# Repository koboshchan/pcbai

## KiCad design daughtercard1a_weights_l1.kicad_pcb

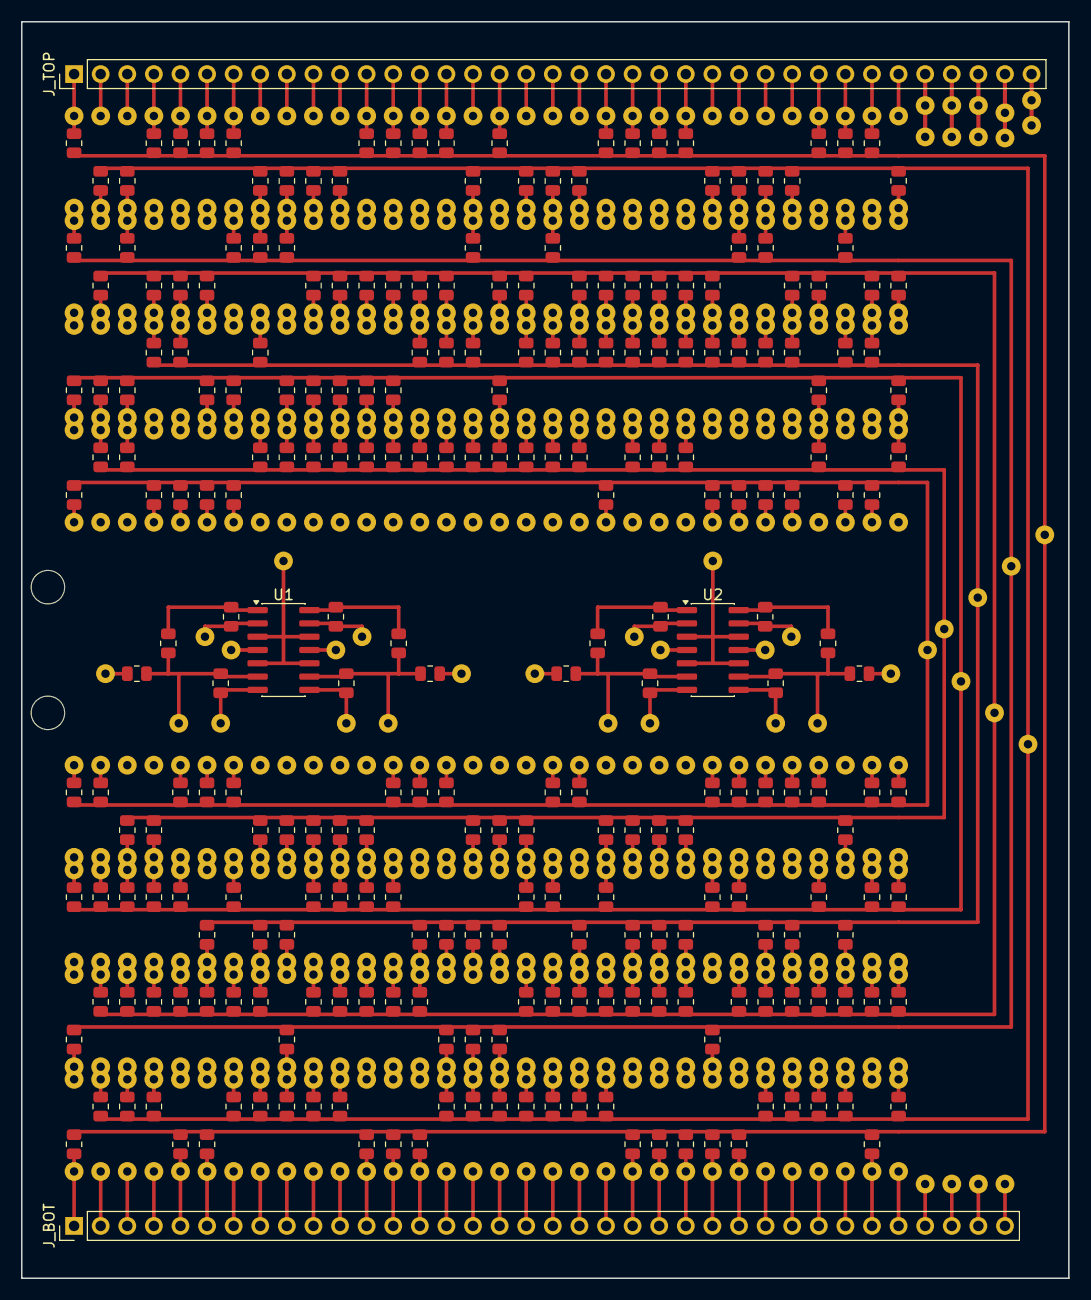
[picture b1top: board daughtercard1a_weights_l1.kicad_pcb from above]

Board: 2 copper layers, 100.0 x 120.0 mm, 556 parts (0 on the bottom side), 85 nets.

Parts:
J_BOT: INPUTS_32_63_SUM; PinHeader_1x36_P2.54mm_Vertical
J_TOP: INPUTS_0_31_PWR; PinHeader_1x37_P2.54mm_Vertical
MH1, MH2: MountingHole_3.2mm_M3
R1_0_0, R1_4_0, R1_7_0, R1_21_0, R1_22_0, R1_26_3, R1_27_0, R1_40_3, R1_55_0, R1_62_0, R1_63_3: 12k; R_0805_2012Metric
R1_0_1, R1_3_3, R1_6_1, R1_13_1, R1_14_1, R1_15_0, R1_25_1, R1_27_1, R1_48_1, R1_50_3: 300k; R_0805_2012Metric
R1_0_2, R1_6_3, R1_11_1, R1_12_1, R1_20_0, R1_30_1, R1_34_2, R1_38_0, R1_38_2, R1_40_0, R1_44_1, R1_45_0, R1_45_1, R1_46_2, R1_49_1, R1_50_1, R1_53_1, R1_53_3, R1_59_1, R1_60_1, R1_62_2: 51k; R_0805_2012Metric
R1_0_3, R1_3_2, R1_11_3, R1_13_2, R1_18_0, R1_27_2, R1_35_2, R1_37_0, R1_48_2, R1_49_0, R1_57_2, R1_60_0: 43k; R_0805_2012Metric
R1_1_0, R1_1_2, R1_7_1, R1_10_0, R1_10_2, R1_16_1, R1_18_1, R1_19_1, R1_20_3, R1_21_3, R1_24_1, R1_28_0, R1_28_3, R1_31_1, R1_33_1, R1_34_1, R1_35_0, R1_36_3, R1_37_1, R1_39_2, R1_39_3, R1_44_2, R1_44_3, R1_46_1, R1_50_0, R1_51_2, R1_52_1, R1_52_3, R1_53_2, R1_54_3, R1_57_0, R1_58_0, R1_58_3, R1_59_0, R1_62_1: 200k; R_0805_2012Metric
R1_1_1, R1_5_3, R1_26_1, R1_31_0, R1_46_3, R1_47_1, R1_48_0: 390k; R_0805_2012Metric
R1_1_3, R1_4_1, R1_5_1, R1_6_0, R1_8_1, R1_10_1, R1_11_0, R1_17_0, R1_22_3, R1_29_3, R1_30_2, R1_32_0, R1_32_1, R1_32_2, R1_35_1, R1_36_2, R1_37_2, R1_42_3, R1_43_0, R1_44_0, R1_46_0, R1_48_3, R1_50_2, R1_51_1, R1_51_3, R1_52_2, R1_53_0, R1_54_1, R1_57_1, R1_59_2, R1_61_2, R1_62_3: 75k; R_0805_2012Metric
R1_2_0, R1_2_2, R1_8_0, R1_8_2, R1_14_2, R1_16_0, R1_18_2, R1_23_3, R1_24_0, R1_26_2, R1_29_0, R1_36_0, R1_38_3, R1_41_3, R1_42_2, R1_43_2, R1_47_3, R1_49_3, R1_54_0, R1_54_2, R1_55_2, R1_55_3, R1_59_3: 22k; R_0805_2012Metric
R1_2_1, R1_2_3, R1_3_0, R1_3_1, R1_9_1, R1_11_2, R1_12_2, R1_12_3, R1_14_3, R1_15_1, R1_17_1, R1_21_1, R1_23_1, R1_28_2, R1_31_3, R1_33_0, R1_33_2, R1_36_1, R1_38_1, R1_39_1, R1_41_1, R1_42_1, R1_43_1, R1_45_3, R1_51_0, R1_52_0, R1_55_1, R1_58_1, R1_58_2, R1_60_2, R1_61_1, R1_63_1: 100k; R_0805_2012Metric
R1_4_2, R1_4_3, R1_5_0, R1_5_2, R1_9_0, R1_9_3, R1_10_3, R1_13_0, R1_14_0, R1_16_2, R1_17_2, R1_19_2, R1_24_2, R1_25_0, R1_26_0, R1_27_3, R1_30_3, R1_33_3, R1_34_0, R1_37_3, R1_40_2, R1_41_2, R1_42_0, R1_43_3, R1_47_0, R1_49_2, R1_56_3, R1_57_3, R1_63_2: 33k; R_0805_2012Metric
R1_6_2, R1_61_0, R1_63_0: 680k; R_0805_2012Metric
R1_7_2, R1_15_2, R1_17_3, R1_19_0, R1_21_2, R1_25_3, R1_56_0: 10k; R_0805_2012Metric
R1_7_3, R1_9_2, R1_19_3, R1_20_2, R1_30_0, R1_41_0: 20k; R_0805_2012Metric
R1_8_3, R1_12_0, R1_35_3: 18k; R_0805_2012Metric
R1_13_3, R1_20_1, R1_22_1, R1_28_1, R1_29_1, R1_40_1, R1_61_3: 1M; R_0805_2012Metric
R1_15_3, R1_18_3, R1_23_0, R1_29_2: 15k; R_0805_2012Metric
R1_16_3, R1_22_2, R1_23_2, R1_24_3, R1_31_2, R1_39_0: 7.5k; R_0805_2012Metric
R1_25_2, R1_45_2, R1_47_2, R1_60_3: 47k; R_0805_2012Metric
R1_32_3: 5.6k; R_0805_2012Metric
R1_34_3, R1_56_2: 470k; R_0805_2012Metric
R1_56_1: DNP; R_0805_2012Metric
Rb_N0: 390k; R_0805_2012Metric
Rb_N1: 470k; R_0805_2012Metric
Rb_N2, Rb_N3: 200k; R_0805_2012Metric
Rc_N0, Rc_N1, Rc_N2, Rc_N3: 10k; R_0805_2012Metric
Rf1_N0, Rf1_N1, Rf1_N2, Rf1_N3: 10k; R_0805_2012Metric
Rf_N0, Rf_N1, Rf_N2, Rf_N3: 10k; R_0805_2012Metric
U1, U2: TL074; SOIC-14_3.9x8.7mm_P1.27mm
W1, W2, W3, W4, W5, W6, W7, W8, W9, W10, W11, W12, W13, W14, W15, W16, W17, W18, W19, W20, W21, W22, W23, W24, W25, W26, W27, W28, W29, W30, W31, W32, W33, W34, W35, W36, W37, W38, W39, W40, W41, W42, W43, W44, W45, W46, W47, W48, W49, W50, W51, W52, W53, W54, W55, W56, W57, W58, W59, W60, W61, W62, W63, W64, W65, W66, W67, W68, W69, W70, W71, W72, W73, W74, W75, W76, W77, W78, W79, W80, W81, W82, W83, W84, W85, W86, W87, W88, W89, W90, W91, W92, W93, W94, W95, W96, W97, W98, W99, W100, W101, W102, W103, W104, W105, W106, W107, W108, W109, W110, W111, W112, W113, W114, W115, W116, W117, W118, W119, W120, W121, W122, W123, W124, W125, W126, W127, W128, W129, W130, W131, W132, W133, W134, W135, W136, W137, W138, W139, W140, W141, W142, W143, W144, W145, W146, W147, W148, W149, W150, W151, W152, W153, W154, W155, W156, W157, W158, W159, W160, W161, W162, W163, W164, W165, W166, W167, W168, W169, W170, W171, W172, W173, W174, W175, W176, W177, W178, W179, W180, W181, W182, W183, W184, W185, W186, W187, W188, W189, W190, W191, W192, W193, W194, W195, W196, W197, W198, W199, W200, W201, W202, W203, W204, W205, W206, W207, W208, W209, W210, W211, W212, W213, W214, W215, W216, W217, W218, W219, W220, W221, W222, W223, W224, W225, W226, W227, W228, W229, W230, W231, W232, W233, W234, W235, W236, W237, W238, W239, W240, W241, W242, W243, W244, W245, W246, W247, W248, W249, W250, W251, W252, W253, W254, W255, W256, W257, W258, W259, W260, W261, W262, W263, W264, W265, W266, W267, W268, W269, W270, W271, W272, W273, W274, W275, W276, W277, W278: JUMPER; Jumper_Wire

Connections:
+5V_REF: J_TOP.36, Rb_N1.2, Rb_N3.2, W270.1, W278.1
+12V: J_TOP.33, U1.4, U2.4, W259.1, W261.1
-5V_REF: J_TOP.37, Rb_N0.1, Rb_N2.1, W266.1, W274.1
-12V: J_TOP.34, U1.11, U2.11, W260.1, W262.1
GND: J_TOP.35, U1.3, U1.5, U1.10, U1.12, U2.3, U2.5, U2.10, U2.12, W257.1, W258.1
IN_0: J_TOP.1, R1_0_0.1, R1_0_1.1, R1_0_2.1, R1_0_3.1, W1.1, W2.1, W3.1, W4.1
IN_1: J_TOP.2, R1_1_0.1, R1_1_1.1, R1_1_2.1, R1_1_3.1, W5.1, W6.1, W7.1, W8.1
IN_2: J_TOP.3, R1_2_0.1, R1_2_1.1, R1_2_2.1, R1_2_3.1, W9.1, W10.1, W11.1, W12.1
IN_3: J_TOP.4, R1_3_0.1, R1_3_1.1, R1_3_2.1, R1_3_3.1, W13.1, W14.1, W15.1, W16.1
IN_4: J_TOP.5, R1_4_0.1, R1_4_1.1, R1_4_2.1, R1_4_3.1, W17.1, W18.1, W19.1, W20.1
IN_5: J_TOP.6, R1_5_0.1, R1_5_1.1, R1_5_2.1, R1_5_3.1, W21.1, W22.1, W23.1, W24.1
IN_6: J_TOP.7, R1_6_0.1, R1_6_1.1, R1_6_2.1, R1_6_3.1, W25.1, W26.1, W27.1, W28.1
IN_7: J_TOP.8, R1_7_0.1, R1_7_1.1, R1_7_2.1, R1_7_3.1, W29.1, W30.1, W31.1, W32.1
IN_8: J_TOP.9, R1_8_0.1, R1_8_1.1, R1_8_2.1, R1_8_3.1, W33.1, W34.1, W35.1, W36.1
IN_9: J_TOP.10, R1_9_0.1, R1_9_1.1, R1_9_2.1, R1_9_3.1, W37.1, W38.1, W39.1, W40.1
IN_10: J_TOP.11, R1_10_0.1, R1_10_1.1, R1_10_2.1, R1_10_3.1, W41.1, W42.1, W43.1, W44.1
IN_11: J_TOP.12, R1_11_0.1, R1_11_1.1, R1_11_2.1, R1_11_3.1, W45.1, W46.1, W47.1, W48.1
IN_12: J_TOP.13, R1_12_0.1, R1_12_1.1, R1_12_2.1, R1_12_3.1, W49.1, W50.1, W51.1, W52.1
IN_13: J_TOP.14, R1_13_0.1, R1_13_1.1, R1_13_2.1, R1_13_3.1, W53.1, W54.1, W55.1, W56.1
IN_14: J_TOP.15, R1_14_0.1, R1_14_1.1, R1_14_2.1, R1_14_3.1, W57.1, W58.1, W59.1, W60.1
IN_15: J_TOP.16, R1_15_0.1, R1_15_1.1, R1_15_2.1, R1_15_3.1, W61.1, W62.1, W63.1, W64.1
IN_16: J_TOP.17, R1_16_0.1, R1_16_1.1, R1_16_2.1, R1_16_3.1, W65.1, W66.1, W67.1, W68.1
IN_17: J_TOP.18, R1_17_0.1, R1_17_1.1, R1_17_2.1, R1_17_3.1, W69.1, W70.1, W71.1, W72.1
IN_18: J_TOP.19, R1_18_0.1, R1_18_1.1, R1_18_2.1, R1_18_3.1, W73.1, W74.1, W75.1, W76.1
IN_19: J_TOP.20, R1_19_0.1, R1_19_1.1, R1_19_2.1, R1_19_3.1, W77.1, W78.1, W79.1, W80.1
IN_20: J_TOP.21, R1_20_0.1, R1_20_1.1, R1_20_2.1, R1_20_3.1, W81.1, W82.1, W83.1, W84.1
IN_21: J_TOP.22, R1_21_0.1, R1_21_1.1, R1_21_2.1, R1_21_3.1, W85.1, W86.1, W87.1, W88.1
IN_22: J_TOP.23, R1_22_0.1, R1_22_1.1, R1_22_2.1, R1_22_3.1, W89.1, W90.1, W91.1, W92.1
IN_23: J_TOP.24, R1_23_0.1, R1_23_1.1, R1_23_2.1, R1_23_3.1, W93.1, W94.1, W95.1, W96.1
IN_24: J_TOP.25, R1_24_0.1, R1_24_1.1, R1_24_2.1, R1_24_3.1, W97.1, W98.1, W99.1, W100.1
IN_25: J_TOP.26, R1_25_0.1, R1_25_1.1, R1_25_2.1, R1_25_3.1, W101.1, W102.1, W103.1, W104.1
IN_26: J_TOP.27, R1_26_0.1, R1_26_1.1, R1_26_2.1, R1_26_3.1, W105.1, W106.1, W107.1, W108.1
IN_27: J_TOP.28, R1_27_0.1, R1_27_1.1, R1_27_2.1, R1_27_3.1, W109.1, W110.1, W111.1, W112.1
IN_28: J_TOP.29, R1_28_0.1, R1_28_1.1, R1_28_2.1, R1_28_3.1, W113.1, W114.1, W115.1, W116.1
IN_29: J_TOP.30, R1_29_0.1, R1_29_1.1, R1_29_2.1, R1_29_3.1, W117.1, W118.1, W119.1, W120.1
IN_30: J_TOP.31, R1_30_0.1, R1_30_1.1, R1_30_2.1, R1_30_3.1, W121.1, W122.1, W123.1, W124.1
IN_31: J_TOP.32, R1_31_0.1, R1_31_1.1, R1_31_2.1, R1_31_3.1, W125.1, W126.1, W127.1, W128.1
IN_32: J_BOT.1, R1_32_0.1, R1_32_1.1, R1_32_2.1, R1_32_3.1, W129.1, W130.1, W131.1, W132.1
IN_33: J_BOT.2, R1_33_0.1, R1_33_1.1, R1_33_2.1, R1_33_3.1, W133.1, W134.1, W135.1, W136.1
IN_34: J_BOT.3, R1_34_0.1, R1_34_1.1, R1_34_2.1, R1_34_3.1, W137.1, W138.1, W139.1, W140.1
IN_35: J_BOT.4, R1_35_0.1, R1_35_1.1, R1_35_2.1, R1_35_3.1, W141.1, W142.1, W143.1, W144.1
IN_36: J_BOT.5, R1_36_0.1, R1_36_1.1, R1_36_2.1, R1_36_3.1, W145.1, W146.1, W147.1, W148.1
IN_37: J_BOT.6, R1_37_0.1, R1_37_1.1, R1_37_2.1, R1_37_3.1, W149.1, W150.1, W151.1, W152.1
IN_38: J_BOT.7, R1_38_0.1, R1_38_1.1, R1_38_2.1, R1_38_3.1, W153.1, W154.1, W155.1, W156.1
IN_39: J_BOT.8, R1_39_0.1, R1_39_1.1, R1_39_2.1, R1_39_3.1, W157.1, W158.1, W159.1, W160.1
IN_40: J_BOT.9, R1_40_0.1, R1_40_1.1, R1_40_2.1, R1_40_3.1, W161.1, W162.1, W163.1, W164.1
IN_41: J_BOT.10, R1_41_0.1, R1_41_1.1, R1_41_2.1, R1_41_3.1, W165.1, W166.1, W167.1, W168.1
IN_42: J_BOT.11, R1_42_0.1, R1_42_1.1, R1_42_2.1, R1_42_3.1, W169.1, W170.1, W171.1, W172.1
IN_43: J_BOT.12, R1_43_0.1, R1_43_1.1, R1_43_2.1, R1_43_3.1, W173.1, W174.1, W175.1, W176.1
IN_44: J_BOT.13, R1_44_0.1, R1_44_1.1, R1_44_2.1, R1_44_3.1, W177.1, W178.1, W179.1, W180.1
IN_45: J_BOT.14, R1_45_0.1, R1_45_1.1, R1_45_2.1, R1_45_3.1, W181.1, W182.1, W183.1, W184.1
IN_46: J_BOT.15, R1_46_0.1, R1_46_1.1, R1_46_2.1, R1_46_3.1, W185.1, W186.1, W187.1, W188.1
IN_47: J_BOT.16, R1_47_0.1, R1_47_1.1, R1_47_2.1, R1_47_3.1, W189.1, W190.1, W191.1, W192.1
IN_48: J_BOT.17, R1_48_0.1, R1_48_1.1, R1_48_2.1, R1_48_3.1, W193.1, W194.1, W195.1, W196.1
IN_49: J_BOT.18, R1_49_0.1, R1_49_1.1, R1_49_2.1, R1_49_3.1, W197.1, W198.1, W199.1, W200.1
IN_50: J_BOT.19, R1_50_0.1, R1_50_1.1, R1_50_2.1, R1_50_3.1, W201.1, W202.1, W203.1, W204.1
IN_51: J_BOT.20, R1_51_0.1, R1_51_1.1, R1_51_2.1, R1_51_3.1, W205.1, W206.1, W207.1, W208.1
IN_52: J_BOT.21, R1_52_0.1, R1_52_1.1, R1_52_2.1, R1_52_3.1, W209.1, W210.1, W211.1, W212.1
IN_53: J_BOT.22, R1_53_0.1, R1_53_1.1, R1_53_2.1, R1_53_3.1, W213.1, W214.1, W215.1, W216.1
IN_54: J_BOT.23, R1_54_0.1, R1_54_1.1, R1_54_2.1, R1_54_3.1, W217.1, W218.1, W219.1, W220.1
IN_55: J_BOT.24, R1_55_0.1, R1_55_1.1, R1_55_2.1, R1_55_3.1, W221.1, W222.1, W223.1, W224.1
IN_56: J_BOT.25, R1_56_0.1, R1_56_1.1, R1_56_2.1, R1_56_3.1, W225.1, W226.1, W227.1, W228.1
IN_57: J_BOT.26, R1_57_0.1, R1_57_1.1, R1_57_2.1, R1_57_3.1, W229.1, W230.1, W231.1, W232.1
IN_58: J_BOT.27, R1_58_0.1, R1_58_1.1, R1_58_2.1, R1_58_3.1, W233.1, W234.1, W235.1, W236.1
IN_59: J_BOT.28, R1_59_0.1, R1_59_1.1, R1_59_2.1, R1_59_3.1, W237.1, W238.1, W239.1, W240.1
IN_60: J_BOT.29, R1_60_0.1, R1_60_1.1, R1_60_2.1, R1_60_3.1, W241.1, W242.1, W243.1, W244.1
IN_61: J_BOT.30, R1_61_0.1, R1_61_1.1, R1_61_2.1, R1_61_3.1, W245.1, W246.1, W247.1, W248.1
IN_62: J_BOT.31, R1_62_0.1, R1_62_1.1, R1_62_2.1, R1_62_3.1, W249.1, W250.1, W251.1, W252.1
IN_63: J_BOT.32, R1_63_0.1, R1_63_1.1, R1_63_2.1, R1_63_3.1, W253.1, W254.1, W255.1, W256.1
SUM_NEG_0: R1_1_0.2, R1_2_0.2, R1_7_0.2, R1_8_0.2, R1_9_0.2, R1_10_0.2, R1_15_0.2, R1_17_0.2, R1_18_0.2, R1_19_0.2, R1_24_0.2, R1_25_0.2, R1_26_0.2, R1_27_0.2, R1_31_0.2, R1_33_0.2, R1_34_0.2, R1_35_0.2, R1_38_0.2, R1_39_0.2, R1_40_0.2, R1_41_0.2, R1_42_0.2, R1_46_0.2, R1_47_0.2, R1_48_0.2, R1_49_0.2, R1_50_0.2, R1_51_0.2, R1_52_0.2, R1_58_0.2, R1_59_0.2, R1_60_0.2, R1_61_0.2, R1_63_0.2, Rb_N0.2, Rc_N0.2, Rf_N0.1, U1.6, W265.1
SUM_NEG_1: R1_1_1.2, R1_3_1.2, R1_4_1.2, R1_5_1.2, R1_9_1.2, R1_10_1.2, R1_11_1.2, R1_12_1.2, R1_13_1.2, R1_14_1.2, R1_16_1.2, R1_17_1.2, R1_19_1.2, R1_20_1.2, R1_21_1.2, R1_22_1.2, R1_23_1.2, R1_24_1.2, R1_27_1.2, R1_28_1.2, R1_30_1.2, R1_31_1.2, R1_33_1.2, R1_34_1.2, R1_35_1.2, R1_36_1.2, R1_37_1.2, R1_38_1.2, R1_39_1.2, R1_41_1.2, R1_42_1.2, R1_43_1.2, R1_44_1.2, R1_45_1.2, R1_49_1.2, R1_50_1.2, R1_51_1.2, R1_52_1.2, R1_53_1.2, R1_54_1.2, R1_55_1.2, R1_57_1.2, R1_58_1.2, R1_59_1.2, R1_60_1.2, R1_61_1.2, R1_62_1.2, R1_63_1.2, Rb_N1.1, Rc_N1.2, Rf_N1.1, U1.9, W269.1
SUM_NEG_2: R1_0_2.2, R1_1_2.2, R1_2_2.2, R1_5_2.2, R1_6_2.2, R1_8_2.2, R1_9_2.2, R1_10_2.2, R1_11_2.2, R1_12_2.2, R1_16_2.2, R1_28_2.2, R1_31_2.2, R1_32_2.2, R1_33_2.2, R1_34_2.2, R1_35_2.2, R1_36_2.2, R1_38_2.2, R1_41_2.2, R1_42_2.2, R1_43_2.2, R1_44_2.2, R1_49_2.2, R1_50_2.2, R1_52_2.2, R1_56_2.2, R1_57_2.2, R1_60_2.2, R1_62_2.2, R1_63_2.2, Rb_N2.2, Rc_N2.2, Rf_N2.1, U2.6, W273.1
SUM_NEG_3: R1_0_3.2, R1_3_3.2, R1_4_3.2, R1_5_3.2, R1_6_3.2, R1_20_3.2, R1_24_3.2, R1_25_3.2, R1_26_3.2, R1_27_3.2, R1_29_3.2, R1_30_3.2, R1_32_3.2, R1_33_3.2, R1_36_3.2, R1_37_3.2, R1_38_3.2, R1_44_3.2, R1_45_3.2, R1_46_3.2, R1_50_3.2, R1_51_3.2, R1_56_3.2, R1_57_3.2, R1_58_3.2, R1_59_3.2, R1_60_3.2, R1_62_3.2, R1_63_3.2, Rb_N3.1, Rc_N3.2, Rf_N3.1, U2.9, W277.1
SUM_POS_0: R1_0_0.2, R1_3_0.2, R1_4_0.2, R1_5_0.2, R1_6_0.2, R1_11_0.2, R1_12_0.2, R1_13_0.2, R1_14_0.2, R1_16_0.2, R1_20_0.2, R1_21_0.2, R1_22_0.2, R1_23_0.2, R1_28_0.2, R1_29_0.2, R1_30_0.2, R1_32_0.2, R1_36_0.2, R1_37_0.2, R1_43_0.2, R1_44_0.2, R1_45_0.2, R1_53_0.2, R1_54_0.2, R1_55_0.2, R1_56_0.2, R1_57_0.2, R1_62_0.2, Rf1_N0.2, U1.2, W263.1
SUM_POS_1: R1_0_1.2, R1_2_1.2, R1_6_1.2, R1_7_1.2, R1_8_1.2, R1_15_1.2, R1_18_1.2, R1_25_1.2, R1_26_1.2, R1_29_1.2, R1_32_1.2, R1_40_1.2, R1_46_1.2, R1_47_1.2, R1_48_1.2, R1_56_1.2, Rf1_N1.2, U1.13, W267.1
SUM_POS_2: R1_3_2.2, R1_4_2.2, R1_7_2.2, R1_13_2.2, R1_14_2.2, R1_15_2.2, R1_17_2.2, R1_18_2.2, R1_19_2.2, R1_20_2.2, R1_21_2.2, R1_22_2.2, R1_23_2.2, R1_24_2.2, R1_25_2.2, R1_26_2.2, R1_27_2.2, R1_29_2.2, R1_30_2.2, R1_37_2.2, R1_39_2.2, R1_40_2.2, R1_45_2.2, R1_46_2.2, R1_47_2.2, R1_48_2.2, R1_51_2.2, R1_53_2.2, R1_54_2.2, R1_55_2.2, R1_58_2.2, R1_59_2.2, R1_61_2.2, Rf1_N2.2, U2.2, W271.1
SUM_POS_3: R1_1_3.2, R1_2_3.2, R1_7_3.2, R1_8_3.2, R1_9_3.2, R1_10_3.2, R1_11_3.2, R1_12_3.2, R1_13_3.2, R1_14_3.2, R1_15_3.2, R1_16_3.2, R1_17_3.2, R1_18_3.2, R1_19_3.2, R1_21_3.2, R1_22_3.2, R1_23_3.2, R1_28_3.2, R1_31_3.2, R1_34_3.2, R1_35_3.2, R1_39_3.2, R1_40_3.2, R1_41_3.2, R1_42_3.2, R1_43_3.2, R1_47_3.2, R1_48_3.2, R1_49_3.2, R1_52_3.2, R1_53_3.2, R1_54_3.2, R1_55_3.2, R1_61_3.2, Rf1_N3.2, U2.13, W275.1
V_INV_0: Rc_N0.1, Rf1_N0.1, U1.1
V_INV_1: Rc_N1.1, Rf1_N1.1, U1.14
V_INV_2: Rc_N2.1, Rf1_N2.1, U2.1
V_INV_3: Rc_N3.1, Rf1_N3.1, U2.14
V_SUM_0: J_BOT.33, Rf_N0.2, U1.7, W264.1
V_SUM_1: J_BOT.34, Rf_N1.2, U1.8, W268.1
V_SUM_2: J_BOT.35, Rf_N2.2, U2.7, W272.1
V_SUM_3: J_BOT.36, Rf_N3.2, U2.8, W276.1

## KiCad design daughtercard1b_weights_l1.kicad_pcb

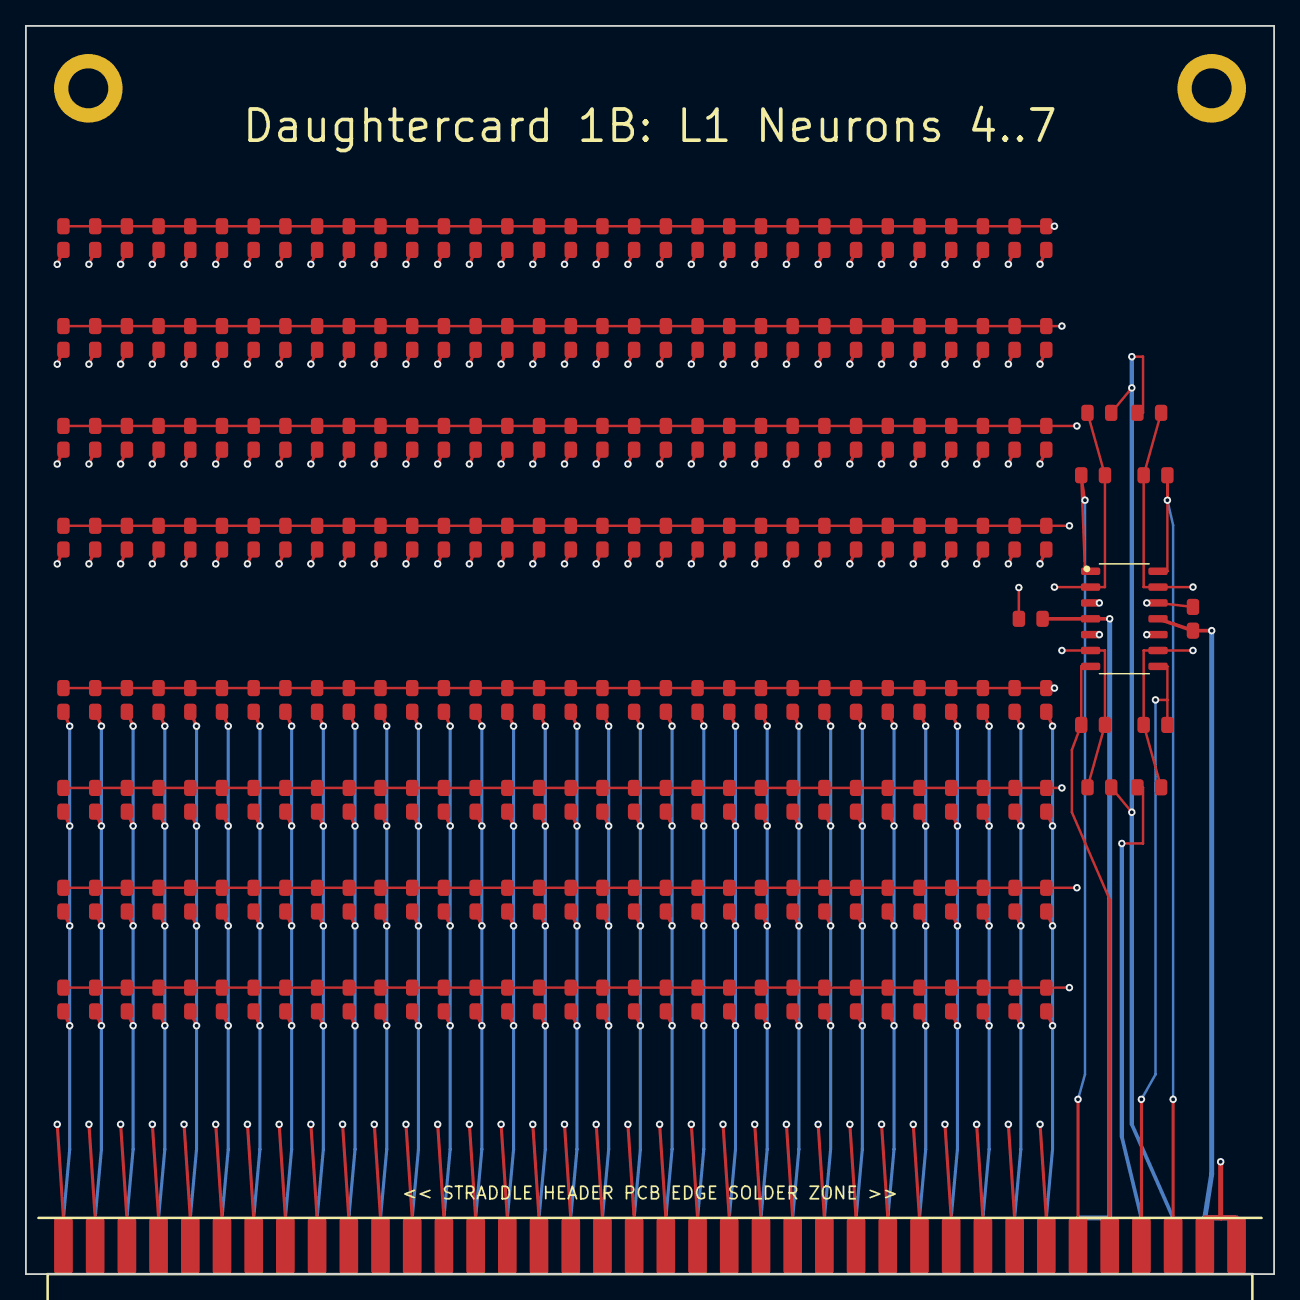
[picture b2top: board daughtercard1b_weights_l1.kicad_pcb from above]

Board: 4 copper layers, 100.0 x 100.0 mm, 270 parts (0 on the bottom side), 77 nets.

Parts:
C_U1N, C_U1P: 0.1uF; C_0805_2012Metric
H1, H2: MountingHole; MountingHole_3.2mm_M3_Pad
J_STRADDLE_EDGE: PinHeader_2x38_Straddle; PinHeader_2x38_Straddle_P2.54mm
R1_0_0, R1_1_3, R1_5_3, R1_6_3, R1_7_2, R1_21_2, R1_22_2, R1_32_0, R1_39_2, R1_42_0, R1_47_3, R1_56_2, R1_62_2: 7.5k; R_0805_2012Metric
R1_0_1, R1_6_2, R1_29_3, R1_41_0: 5.6k; R_0805_2012Metric
R1_0_2, R1_1_0, R1_3_1, R1_3_3, R1_8_0, R1_8_1, R1_10_1, R1_27_0, R1_28_2, R1_28_3, R1_33_2, R1_36_0, R1_40_2, R1_41_1, R1_45_2, R1_46_2, R1_48_2, R1_54_0, R1_57_3, R1_62_1: 18k; R_0805_2012Metric
R1_0_3, R1_40_0, R1_56_1: 5.1k; R_0805_2012Metric
R1_1_1, R1_1_2, R1_6_1, R1_7_0, R1_9_0, R1_10_0, R1_10_2, R1_11_2, R1_21_3, R1_25_3, R1_29_0, R1_35_2, R1_42_2, R1_42_3, R1_44_2, R1_47_2, R1_48_1, R1_53_2, R1_55_0, R1_56_0, R1_56_3, R1_58_1, R1_60_0, R1_60_1: 43k; R_0805_2012Metric
R1_2_0, R1_3_2, R1_15_1, R1_17_1, R1_17_3, R1_22_1, R1_26_0, R1_26_1, R1_33_0, R1_34_0, R1_37_0, R1_37_1, R1_49_3, R1_55_2, R1_58_3, R1_59_0, R1_60_3, R1_61_3: 51k; R_0805_2012Metric
R1_2_1, R1_3_0, R1_4_0, R1_5_1, R1_8_2, R1_11_1, R1_12_2, R1_13_3, R1_14_3, R1_16_0, R1_18_0, R1_23_0, R1_29_2, R1_33_3, R1_35_1, R1_36_2, R1_37_3, R1_44_0, R1_44_3, R1_45_0, R1_45_1, R1_53_0, R1_54_3, R1_57_2, R1_58_0, R1_59_1, R1_60_2, R1_61_0, R1_62_0: 33k; R_0805_2012Metric
R1_2_2, R1_21_1, R1_24_2, R1_41_3: 300k; R_0805_2012Metric
R1_2_3, R1_4_1, R1_11_0, R1_15_0, R1_19_1, R1_19_2, R1_20_0, R1_20_1, R1_24_3, R1_28_0, R1_32_2, R1_32_3, R1_33_1, R1_34_1, R1_38_2, R1_43_2, R1_46_0, R1_46_3, R1_51_1, R1_54_2, R1_59_3, R1_62_3, R1_63_1, R1_63_2: 22k; R_0805_2012Metric
R1_4_2, R1_24_1, R1_30_0, R1_30_2, R1_31_1, R1_38_0, R1_38_3, R1_39_0, R1_43_1, R1_48_0, R1_50_0, R1_51_0: 15k; R_0805_2012Metric
R1_4_3, R1_5_2, R1_8_3, R1_20_2, R1_22_3, R1_31_0, R1_32_1, R1_42_1, R1_43_0, R1_55_3, R1_63_0: 10k; R_0805_2012Metric
R1_5_0, R1_12_0, R1_57_0: 47k; R_0805_2012Metric
R1_6_0, R1_7_3, R1_14_2, R1_15_3, R1_16_2, R1_16_3, R1_23_1, R1_24_0, R1_27_1, R1_40_1, R1_47_1, R1_49_0: 12k; R_0805_2012Metric
R1_7_1, R1_23_2, R1_31_2, R1_63_3: 4.7k; R_0805_2012Metric
R1_9_1, R1_9_3, R1_10_3, R1_12_3, R1_19_0, R1_21_0, R1_29_1, R1_34_2, R1_36_3, R1_37_2, R1_38_1, R1_43_3, R1_46_1, R1_51_2, R1_52_3, R1_53_3, R1_58_2: 100k; R_0805_2012Metric
R1_9_2, R1_14_0, R1_18_3, R1_25_1, R1_27_2, R1_30_1, R1_35_3, R1_36_1, R1_45_3, R1_47_0, R1_48_3, R1_49_2, R1_50_2, R1_52_1, R1_54_1, R1_57_1, R1_59_2, R1_61_1, R1_61_2: 75k; R_0805_2012Metric
R1_11_3, R1_12_1, R1_17_2, R1_26_2, R1_27_3, R1_34_3, R1_50_3, R1_52_2, R1_53_1: 1M; R_0805_2012Metric
R1_13_0, R1_13_1, R1_14_1, R1_16_1, R1_18_1, R1_41_2, R1_49_1, R1_55_1: 200k; R_0805_2012Metric
R1_13_2, R1_25_0, R1_28_1, R1_35_0, R1_39_1, R1_40_3, R1_44_1, R1_52_0: 20k; R_0805_2012Metric
R1_15_2, R1_31_3: 3.3k; R_0805_2012Metric
R1_17_0, R1_20_3, R1_51_3: 390k; R_0805_2012Metric
R1_18_2, R1_19_3, R1_22_0, R1_25_2, R1_26_3, R1_50_1: 470k; R_0805_2012Metric
R1_23_3, R1_39_3: 3k; R_0805_2012Metric
R1_30_3: 2.2k; R_0805_2012Metric
Rb_N4: 22k; R_0805_2012Metric
Rb_N5, Rb_N7: 33k; R_0805_2012Metric
Rb_N6: 100k; R_0805_2012Metric
Rf_N4, Rf_N5, Rf_N6, Rf_N7: 10k; R_0805_2012Metric
U1: TL074; SOIC-14_3.9x8.7mm_P1.27mm

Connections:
+5V_REF: J_STRADDLE_EDGE.B35, Rb_N6.1
+12V: C_U1P.2, J_STRADDLE_EDGE.B33, J_STRADDLE_EDGE.B34, U1.4
-5V_REF: J_STRADDLE_EDGE.B36, Rb_N4.2, Rb_N5.2, Rb_N7.1
-12V: C_U1N.1, J_STRADDLE_EDGE.B37, J_STRADDLE_EDGE.B38, U1.11
GND: C_U1N.2, C_U1P.1, H1.1, H2.1, J_STRADDLE_EDGE.A37, J_STRADDLE_EDGE.A38, U1.3, U1.5, U1.10, U1.12
INV_N4: R1_0_0.2, R1_1_0.2, R1_2_0.2, R1_3_0.2, R1_4_0.2, R1_5_0.2, R1_6_0.2, R1_7_0.2, R1_8_0.2, R1_9_0.2, R1_10_0.2, R1_11_0.2, R1_12_0.2, R1_13_0.2, R1_14_0.2, R1_15_0.2, R1_16_0.2, R1_17_0.2, R1_18_0.2, R1_19_0.2, R1_20_0.2, R1_21_0.2, R1_22_0.2, R1_23_0.2, R1_24_0.2, R1_25_0.2, R1_26_0.2, R1_27_0.2, R1_28_0.2, R1_29_0.2, R1_30_0.2, R1_31_0.2, R1_32_0.2, R1_33_0.2, R1_34_0.2, R1_35_0.2, R1_36_0.2, R1_37_0.2, R1_38_0.2, R1_39_0.2, R1_40_0.2, R1_41_0.2, R1_42_0.2, R1_43_0.2, R1_44_0.2, R1_45_0.2, R1_46_0.2, R1_47_0.2, R1_48_0.2, R1_49_0.2, R1_50_0.2, R1_51_0.2, R1_52_0.2, R1_53_0.2, R1_54_0.2, R1_55_0.2, R1_56_0.2, R1_57_0.2, R1_58_0.2, R1_59_0.2, R1_60_0.2, R1_61_0.2, R1_62_0.2, R1_63_0.2, Rb_N4.1, Rf_N4.2, U1.2
INV_N5: R1_0_1.2, R1_1_1.2, R1_2_1.2, R1_3_1.2, R1_4_1.2, R1_5_1.2, R1_6_1.2, R1_7_1.2, R1_8_1.2, R1_9_1.2, R1_10_1.2, R1_11_1.2, R1_12_1.2, R1_13_1.2, R1_14_1.2, R1_15_1.2, R1_16_1.2, R1_17_1.2, R1_18_1.2, R1_19_1.2, R1_20_1.2, R1_21_1.2, R1_22_1.2, R1_23_1.2, R1_24_1.2, R1_25_1.2, R1_26_1.2, R1_27_1.2, R1_28_1.2, R1_29_1.2, R1_30_1.2, R1_31_1.2, R1_32_1.2, R1_33_1.2, R1_34_1.2, R1_35_1.2, R1_36_1.2, R1_37_1.2, R1_38_1.2, R1_39_1.2, R1_40_1.2, R1_41_1.2, R1_42_1.2, R1_43_1.2, R1_44_1.2, R1_45_1.2, R1_46_1.2, R1_47_1.2, R1_48_1.2, R1_49_1.2, R1_50_1.2, R1_51_1.2, R1_52_1.2, R1_53_1.2, R1_54_1.2, R1_55_1.2, R1_56_1.2, R1_57_1.2, R1_58_1.2, R1_59_1.2, R1_60_1.2, R1_61_1.2, R1_62_1.2, R1_63_1.2, Rb_N5.1, Rf_N5.2, U1.6
INV_N6: R1_0_2.2, R1_1_2.2, R1_2_2.2, R1_3_2.2, R1_4_2.2, R1_5_2.2, R1_6_2.2, R1_7_2.2, R1_8_2.2, R1_9_2.2, R1_10_2.2, R1_11_2.2, R1_12_2.2, R1_13_2.2, R1_14_2.2, R1_15_2.2, R1_16_2.2, R1_17_2.2, R1_18_2.2, R1_19_2.2, R1_20_2.2, R1_21_2.2, R1_22_2.2, R1_23_2.2, R1_24_2.2, R1_25_2.2, R1_26_2.2, R1_27_2.2, R1_28_2.2, R1_29_2.2, R1_30_2.2, R1_31_2.2, R1_32_2.2, R1_33_2.2, R1_34_2.2, R1_35_2.2, R1_36_2.2, R1_37_2.2, R1_38_2.2, R1_39_2.2, R1_40_2.2, R1_41_2.2, R1_42_2.2, R1_43_2.2, R1_44_2.2, R1_45_2.2, R1_46_2.2, R1_47_2.2, R1_48_2.2, R1_49_2.2, R1_50_2.2, R1_51_2.2, R1_52_2.2, R1_53_2.2, R1_54_2.2, R1_55_2.2, R1_56_2.2, R1_57_2.2, R1_58_2.2, R1_59_2.2, R1_60_2.2, R1_61_2.2, R1_62_2.2, R1_63_2.2, Rb_N6.2, Rf_N6.1, U1.9
INV_N7: R1_0_3.2, R1_1_3.2, R1_2_3.2, R1_3_3.2, R1_4_3.2, R1_5_3.2, R1_6_3.2, R1_7_3.2, R1_8_3.2, R1_9_3.2, R1_10_3.2, R1_11_3.2, R1_12_3.2, R1_13_3.2, R1_14_3.2, R1_15_3.2, R1_16_3.2, R1_17_3.2, R1_18_3.2, R1_19_3.2, R1_20_3.2, R1_21_3.2, R1_22_3.2, R1_23_3.2, R1_24_3.2, R1_25_3.2, R1_26_3.2, R1_27_3.2, R1_28_3.2, R1_29_3.2, R1_30_3.2, R1_31_3.2, R1_32_3.2, R1_33_3.2, R1_34_3.2, R1_35_3.2, R1_36_3.2, R1_37_3.2, R1_38_3.2, R1_39_3.2, R1_40_3.2, R1_41_3.2, R1_42_3.2, R1_43_3.2, R1_44_3.2, R1_45_3.2, R1_46_3.2, R1_47_3.2, R1_48_3.2, R1_49_3.2, R1_50_3.2, R1_51_3.2, R1_52_3.2, R1_53_3.2, R1_54_3.2, R1_55_3.2, R1_56_3.2, R1_57_3.2, R1_58_3.2, R1_59_3.2, R1_60_3.2, R1_61_3.2, R1_62_3.2, R1_63_3.2, Rb_N7.2, Rf_N7.1, U1.13
IN_0: J_STRADDLE_EDGE.A1, R1_0_0.1, R1_0_1.1, R1_0_2.1, R1_0_3.1
IN_1: J_STRADDLE_EDGE.A2, R1_1_0.1, R1_1_1.1, R1_1_2.1, R1_1_3.1
IN_2: J_STRADDLE_EDGE.A3, R1_2_0.1, R1_2_1.1, R1_2_2.1, R1_2_3.1
IN_3: J_STRADDLE_EDGE.A4, R1_3_0.1, R1_3_1.1, R1_3_2.1, R1_3_3.1
IN_4: J_STRADDLE_EDGE.A5, R1_4_0.1, R1_4_1.1, R1_4_2.1, R1_4_3.1
IN_5: J_STRADDLE_EDGE.A6, R1_5_0.1, R1_5_1.1, R1_5_2.1, R1_5_3.1
IN_6: J_STRADDLE_EDGE.A7, R1_6_0.1, R1_6_1.1, R1_6_2.1, R1_6_3.1
IN_7: J_STRADDLE_EDGE.A8, R1_7_0.1, R1_7_1.1, R1_7_2.1, R1_7_3.1
IN_8: J_STRADDLE_EDGE.A9, R1_8_0.1, R1_8_1.1, R1_8_2.1, R1_8_3.1
IN_9: J_STRADDLE_EDGE.A10, R1_9_0.1, R1_9_1.1, R1_9_2.1, R1_9_3.1
IN_10: J_STRADDLE_EDGE.A11, R1_10_0.1, R1_10_1.1, R1_10_2.1, R1_10_3.1
IN_11: J_STRADDLE_EDGE.A12, R1_11_0.1, R1_11_1.1, R1_11_2.1, R1_11_3.1
IN_12: J_STRADDLE_EDGE.A13, R1_12_0.1, R1_12_1.1, R1_12_2.1, R1_12_3.1
IN_13: J_STRADDLE_EDGE.A14, R1_13_0.1, R1_13_1.1, R1_13_2.1, R1_13_3.1
IN_14: J_STRADDLE_EDGE.A15, R1_14_0.1, R1_14_1.1, R1_14_2.1, R1_14_3.1
IN_15: J_STRADDLE_EDGE.A16, R1_15_0.1, R1_15_1.1, R1_15_2.1, R1_15_3.1
IN_16: J_STRADDLE_EDGE.A17, R1_16_0.1, R1_16_1.1, R1_16_2.1, R1_16_3.1
IN_17: J_STRADDLE_EDGE.A18, R1_17_0.1, R1_17_1.1, R1_17_2.1, R1_17_3.1
IN_18: J_STRADDLE_EDGE.A19, R1_18_0.1, R1_18_1.1, R1_18_2.1, R1_18_3.1
IN_19: J_STRADDLE_EDGE.A20, R1_19_0.1, R1_19_1.1, R1_19_2.1, R1_19_3.1
IN_20: J_STRADDLE_EDGE.A21, R1_20_0.1, R1_20_1.1, R1_20_2.1, R1_20_3.1
IN_21: J_STRADDLE_EDGE.A22, R1_21_0.1, R1_21_1.1, R1_21_2.1, R1_21_3.1
IN_22: J_STRADDLE_EDGE.A23, R1_22_0.1, R1_22_1.1, R1_22_2.1, R1_22_3.1
IN_23: J_STRADDLE_EDGE.A24, R1_23_0.1, R1_23_1.1, R1_23_2.1, R1_23_3.1
IN_24: J_STRADDLE_EDGE.A25, R1_24_0.1, R1_24_1.1, R1_24_2.1, R1_24_3.1
IN_25: J_STRADDLE_EDGE.A26, R1_25_0.1, R1_25_1.1, R1_25_2.1, R1_25_3.1
IN_26: J_STRADDLE_EDGE.A27, R1_26_0.1, R1_26_1.1, R1_26_2.1, R1_26_3.1
IN_27: J_STRADDLE_EDGE.A28, R1_27_0.1, R1_27_1.1, R1_27_2.1, R1_27_3.1
IN_28: J_STRADDLE_EDGE.A29, R1_28_0.1, R1_28_1.1, R1_28_2.1, R1_28_3.1
IN_29: J_STRADDLE_EDGE.A30, R1_29_0.1, R1_29_1.1, R1_29_2.1, R1_29_3.1
IN_30: J_STRADDLE_EDGE.A31, R1_30_0.1, R1_30_1.1, R1_30_2.1, R1_30_3.1
IN_31: J_STRADDLE_EDGE.A32, R1_31_0.1, R1_31_1.1, R1_31_2.1, R1_31_3.1
IN_32: J_STRADDLE_EDGE.B1, R1_32_0.1, R1_32_1.1, R1_32_2.1, R1_32_3.1
IN_33: J_STRADDLE_EDGE.B2, R1_33_0.1, R1_33_1.1, R1_33_2.1, R1_33_3.1
IN_34: J_STRADDLE_EDGE.B3, R1_34_0.1, R1_34_1.1, R1_34_2.1, R1_34_3.1
IN_35: J_STRADDLE_EDGE.B4, R1_35_0.1, R1_35_1.1, R1_35_2.1, R1_35_3.1
IN_36: J_STRADDLE_EDGE.B5, R1_36_0.1, R1_36_1.1, R1_36_2.1, R1_36_3.1
IN_37: J_STRADDLE_EDGE.B6, R1_37_0.1, R1_37_1.1, R1_37_2.1, R1_37_3.1
IN_38: J_STRADDLE_EDGE.B7, R1_38_0.1, R1_38_1.1, R1_38_2.1, R1_38_3.1
IN_39: J_STRADDLE_EDGE.B8, R1_39_0.1, R1_39_1.1, R1_39_2.1, R1_39_3.1
IN_40: J_STRADDLE_EDGE.B9, R1_40_0.1, R1_40_1.1, R1_40_2.1, R1_40_3.1
IN_41: J_STRADDLE_EDGE.B10, R1_41_0.1, R1_41_1.1, R1_41_2.1, R1_41_3.1
IN_42: J_STRADDLE_EDGE.B11, R1_42_0.1, R1_42_1.1, R1_42_2.1, R1_42_3.1
IN_43: J_STRADDLE_EDGE.B12, R1_43_0.1, R1_43_1.1, R1_43_2.1, R1_43_3.1
IN_44: J_STRADDLE_EDGE.B13, R1_44_0.1, R1_44_1.1, R1_44_2.1, R1_44_3.1
IN_45: J_STRADDLE_EDGE.B14, R1_45_0.1, R1_45_1.1, R1_45_2.1, R1_45_3.1
IN_46: J_STRADDLE_EDGE.B15, R1_46_0.1, R1_46_1.1, R1_46_2.1, R1_46_3.1
IN_47: J_STRADDLE_EDGE.B16, R1_47_0.1, R1_47_1.1, R1_47_2.1, R1_47_3.1
IN_48: J_STRADDLE_EDGE.B17, R1_48_0.1, R1_48_1.1, R1_48_2.1, R1_48_3.1
IN_49: J_STRADDLE_EDGE.B18, R1_49_0.1, R1_49_1.1, R1_49_2.1, R1_49_3.1
IN_50: J_STRADDLE_EDGE.B19, R1_50_0.1, R1_50_1.1, R1_50_2.1, R1_50_3.1
IN_51: J_STRADDLE_EDGE.B20, R1_51_0.1, R1_51_1.1, R1_51_2.1, R1_51_3.1
IN_52: J_STRADDLE_EDGE.B21, R1_52_0.1, R1_52_1.1, R1_52_2.1, R1_52_3.1
IN_53: J_STRADDLE_EDGE.B22, R1_53_0.1, R1_53_1.1, R1_53_2.1, R1_53_3.1
IN_54: J_STRADDLE_EDGE.B23, R1_54_0.1, R1_54_1.1, R1_54_2.1, R1_54_3.1
IN_55: J_STRADDLE_EDGE.B24, R1_55_0.1, R1_55_1.1, R1_55_2.1, R1_55_3.1
IN_56: J_STRADDLE_EDGE.B25, R1_56_0.1, R1_56_1.1, R1_56_2.1, R1_56_3.1
IN_57: J_STRADDLE_EDGE.B26, R1_57_0.1, R1_57_1.1, R1_57_2.1, R1_57_3.1
IN_58: J_STRADDLE_EDGE.B27, R1_58_0.1, R1_58_1.1, R1_58_2.1, R1_58_3.1
IN_59: J_STRADDLE_EDGE.B28, R1_59_0.1, R1_59_1.1, R1_59_2.1, R1_59_3.1
IN_60: J_STRADDLE_EDGE.B29, R1_60_0.1, R1_60_1.1, R1_60_2.1, R1_60_3.1
IN_61: J_STRADDLE_EDGE.B30, R1_61_0.1, R1_61_1.1, R1_61_2.1, R1_61_3.1
IN_62: J_STRADDLE_EDGE.B31, R1_62_0.1, R1_62_1.1, R1_62_2.1, R1_62_3.1
IN_63: J_STRADDLE_EDGE.B32, R1_63_0.1, R1_63_1.1, R1_63_2.1, R1_63_3.1
V_SUM_4: J_STRADDLE_EDGE.A33, Rf_N4.1, U1.1
V_SUM_5: J_STRADDLE_EDGE.A34, Rf_N5.1, U1.7
V_SUM_6: J_STRADDLE_EDGE.A35, Rf_N6.2, U1.8
V_SUM_7: J_STRADDLE_EDGE.A36, Rf_N7.2, U1.14

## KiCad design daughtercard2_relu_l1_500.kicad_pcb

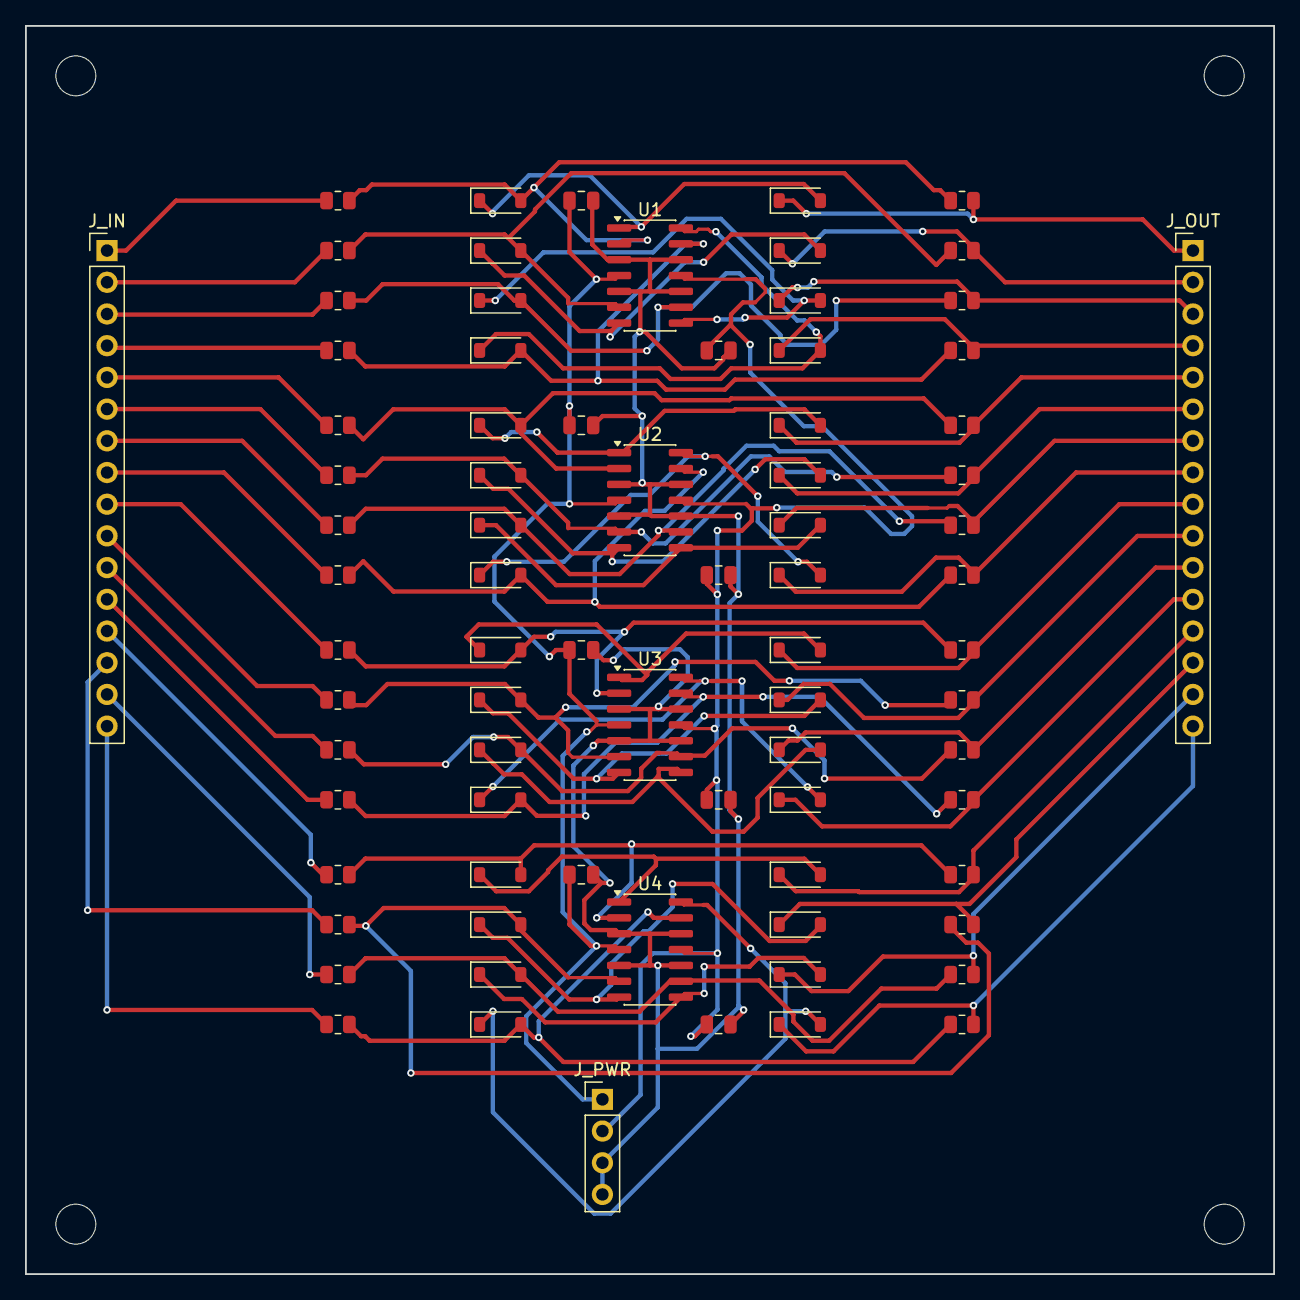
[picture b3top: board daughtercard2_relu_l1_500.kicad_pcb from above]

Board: 2 copper layers, 100.0 x 100.0 mm, 83 parts (0 on the bottom side), 67 nets.

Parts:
C_1_NEG, C_1_POS, C_2_NEG, C_2_POS, C_3_NEG, C_3_POS, C_4_NEG, C_4_POS: 100n; C_0805_2012Metric
D_FB_0, D_FB_1, D_FB_2, D_FB_3, D_FB_4, D_FB_5, D_FB_6, D_FB_7, D_FB_8, D_FB_9, D_FB_10, D_FB_11, D_FB_12, D_FB_13, D_FB_14, D_FB_15: 1N4148; D_SOD-123
D_OUT_0, D_OUT_1, D_OUT_2, D_OUT_3, D_OUT_4, D_OUT_5, D_OUT_6, D_OUT_7, D_OUT_8, D_OUT_9, D_OUT_10, D_OUT_11, D_OUT_12, D_OUT_13, D_OUT_14, D_OUT_15: 1N4148; D_SOD-123
J_IN: V_SUM_IN; PinHeader_1x16_P2.54mm_Vertical
J_OUT: ACT_OUT; PinHeader_1x16_P2.54mm_Vertical
J_PWR: POWER; PinHeader_1x04_P2.54mm_Vertical
MH1, MH2, MH3, MH4: MountingHole_3.2mm_M3
R_FB_0, R_FB_1, R_FB_2, R_FB_3, R_FB_4, R_FB_5, R_FB_6, R_FB_7, R_FB_8, R_FB_9, R_FB_10, R_FB_11, R_FB_12, R_FB_13, R_FB_14, R_FB_15: 10k; R_0805_2012Metric
R_IN_0, R_IN_1, R_IN_2, R_IN_3, R_IN_4, R_IN_5, R_IN_6, R_IN_7, R_IN_8, R_IN_9, R_IN_10, R_IN_11, R_IN_12, R_IN_13, R_IN_14, R_IN_15: 10k; R_0805_2012Metric
U1, U2, U3, U4: TL074; SOIC-14_3.9x8.7mm_P1.27mm

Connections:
+12V: C_1_POS.1, C_2_POS.1, C_3_POS.1, C_4_POS.1, J_PWR.1, U1.4, U2.4, U3.4, U4.4
-12V: C_1_NEG.1, C_2_NEG.1, C_3_NEG.1, C_4_NEG.1, J_PWR.2, U1.11, U2.11, U3.11, U4.11
ACT_0: D_OUT_0.1, J_OUT.1, R_FB_0.2
ACT_1: D_OUT_1.1, J_OUT.2, R_FB_1.2
ACT_2: D_OUT_2.1, J_OUT.3, R_FB_2.2
ACT_3: D_OUT_3.1, J_OUT.4, R_FB_3.2
ACT_4: D_OUT_4.1, J_OUT.5, R_FB_4.2
ACT_5: D_OUT_5.1, J_OUT.6, R_FB_5.2
ACT_6: D_OUT_6.1, J_OUT.7, R_FB_6.2
ACT_7: D_OUT_7.1, J_OUT.8, R_FB_7.2
ACT_8: D_OUT_8.1, J_OUT.9, R_FB_8.2
ACT_9: D_OUT_9.1, J_OUT.10, R_FB_9.2
ACT_10: D_OUT_10.1, J_OUT.11, R_FB_10.2
ACT_11: D_OUT_11.1, J_OUT.12, R_FB_11.2
ACT_12: D_OUT_12.1, J_OUT.13, R_FB_12.2
ACT_13: D_OUT_13.1, J_OUT.14, R_FB_13.2
ACT_14: D_OUT_14.1, J_OUT.15, R_FB_14.2
ACT_15: D_OUT_15.1, J_OUT.16, R_FB_15.2
GND: C_1_NEG.2, C_1_POS.2, C_2_NEG.2, C_2_POS.2, C_3_NEG.2, C_3_POS.2, C_4_NEG.2, C_4_POS.2, J_PWR.3, J_PWR.4, U1.3, U1.5, U1.10, U1.12, U2.3, U2.5, U2.10, U2.12, U3.3, U3.5, U3.10, U3.12, U4.3, U4.5, U4.10, U4.12
INV_IN_0: D_FB_0.2, R_FB_0.1, R_IN_0.2, U1.2
INV_IN_1: D_FB_1.2, R_FB_1.1, R_IN_1.2, U1.6
INV_IN_2: D_FB_2.2, R_FB_2.1, R_IN_2.2, U1.9
INV_IN_3: D_FB_3.2, R_FB_3.1, R_IN_3.2, U1.13
INV_IN_4: D_FB_4.2, R_FB_4.1, R_IN_4.2, U2.2
INV_IN_5: D_FB_5.2, R_FB_5.1, R_IN_5.2, U2.6
INV_IN_6: D_FB_6.2, R_FB_6.1, R_IN_6.2, U2.9
INV_IN_7: D_FB_7.2, R_FB_7.1, R_IN_7.2, U2.13
INV_IN_8: D_FB_8.2, R_FB_8.1, R_IN_8.2, U3.2
INV_IN_9: D_FB_9.2, R_FB_9.1, R_IN_9.2, U3.6
INV_IN_10: D_FB_10.2, R_FB_10.1, R_IN_10.2, U3.9
INV_IN_11: D_FB_11.2, R_FB_11.1, R_IN_11.2, U3.13
INV_IN_12: D_FB_12.2, R_FB_12.1, R_IN_12.2, U4.2
INV_IN_13: D_FB_13.2, R_FB_13.1, R_IN_13.2, U4.6
INV_IN_14: D_FB_14.2, R_FB_14.1, R_IN_14.2, U4.9
INV_IN_15: D_FB_15.2, R_FB_15.1, R_IN_15.2, U4.13
OP_OUT_0: D_FB_0.1, D_OUT_0.2, U1.1
OP_OUT_1: D_FB_1.1, D_OUT_1.2, U1.7
OP_OUT_2: D_FB_2.1, D_OUT_2.2, U1.8
OP_OUT_3: D_FB_3.1, D_OUT_3.2, U1.14
OP_OUT_4: D_FB_4.1, D_OUT_4.2, U2.1
OP_OUT_5: D_FB_5.1, D_OUT_5.2, U2.7
OP_OUT_6: D_FB_6.1, D_OUT_6.2, U2.8
OP_OUT_7: D_FB_7.1, D_OUT_7.2, U2.14
OP_OUT_8: D_FB_8.1, D_OUT_8.2, U3.1
OP_OUT_9: D_FB_9.1, D_OUT_9.2, U3.7
OP_OUT_10: D_FB_10.1, D_OUT_10.2, U3.8
OP_OUT_11: D_FB_11.1, D_OUT_11.2, U3.14
OP_OUT_12: D_FB_12.1, D_OUT_12.2, U4.1
OP_OUT_13: D_FB_13.1, D_OUT_13.2, U4.7
OP_OUT_14: D_FB_14.1, D_OUT_14.2, U4.8
OP_OUT_15: D_FB_15.1, D_OUT_15.2, U4.14
V_SUM_0: J_IN.1, R_IN_0.1
V_SUM_1: J_IN.2, R_IN_1.1
V_SUM_2: J_IN.3, R_IN_2.1
V_SUM_3: J_IN.4, R_IN_3.1
V_SUM_4: J_IN.5, R_IN_4.1
V_SUM_5: J_IN.6, R_IN_5.1
V_SUM_6: J_IN.7, R_IN_6.1
V_SUM_7: J_IN.8, R_IN_7.1
V_SUM_8: J_IN.9, R_IN_8.1
V_SUM_9: J_IN.10, R_IN_9.1
V_SUM_10: J_IN.11, R_IN_10.1
V_SUM_11: J_IN.12, R_IN_11.1
V_SUM_12: J_IN.13, R_IN_12.1
V_SUM_13: J_IN.14, R_IN_13.1
V_SUM_14: J_IN.15, R_IN_14.1
V_SUM_15: J_IN.16, R_IN_15.1
